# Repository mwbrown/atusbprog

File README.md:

# atusbprog

This project is intended as an exercise in learning about the following:

- Silicon Labs EFM8UB1 USB-enabled 8051 microcontroller
- Simplicity Studio for programming the EFM8UB1
- LibUSB on Linux (and possibly Windows?)
- USB in general i.e. for interacting with a microcontroller
- KiCAD design of a daughter card for the EFM8UB1 SLSTK2000A 

# Status

Currently, this project is in the very early stages where only experimentation between Linux and the SLSTK2000A have been done to toggle some LEDs, etc.

This will eventually be used as the foundation of a command/response type device that can be used to program Atmel microcontrollers. In order to accomplish this, a daughter card with one of these microcontrollers will be designed to be plugged into the side of an SLSTK2000A as an exercise in PCB design. This is not strictly required, per-se as the micros can be wired over to a breadboard, but the PCB design will prove to be a useful learning experience.

# Planned Device Support

Current plans for device support are AT89S series C51-based microcontrollers, due to their simple SPI-based programming protocol. If flash space allows, a potential addition would be supporting AVR serial programming.

A preliminary list of devices is:

* AT89S52
  - This will require some level-shifting due to the required 5V supply.
* AT89S8253
  - This can interface directly with the EFM8UB1 due to both being 3.3V chips.

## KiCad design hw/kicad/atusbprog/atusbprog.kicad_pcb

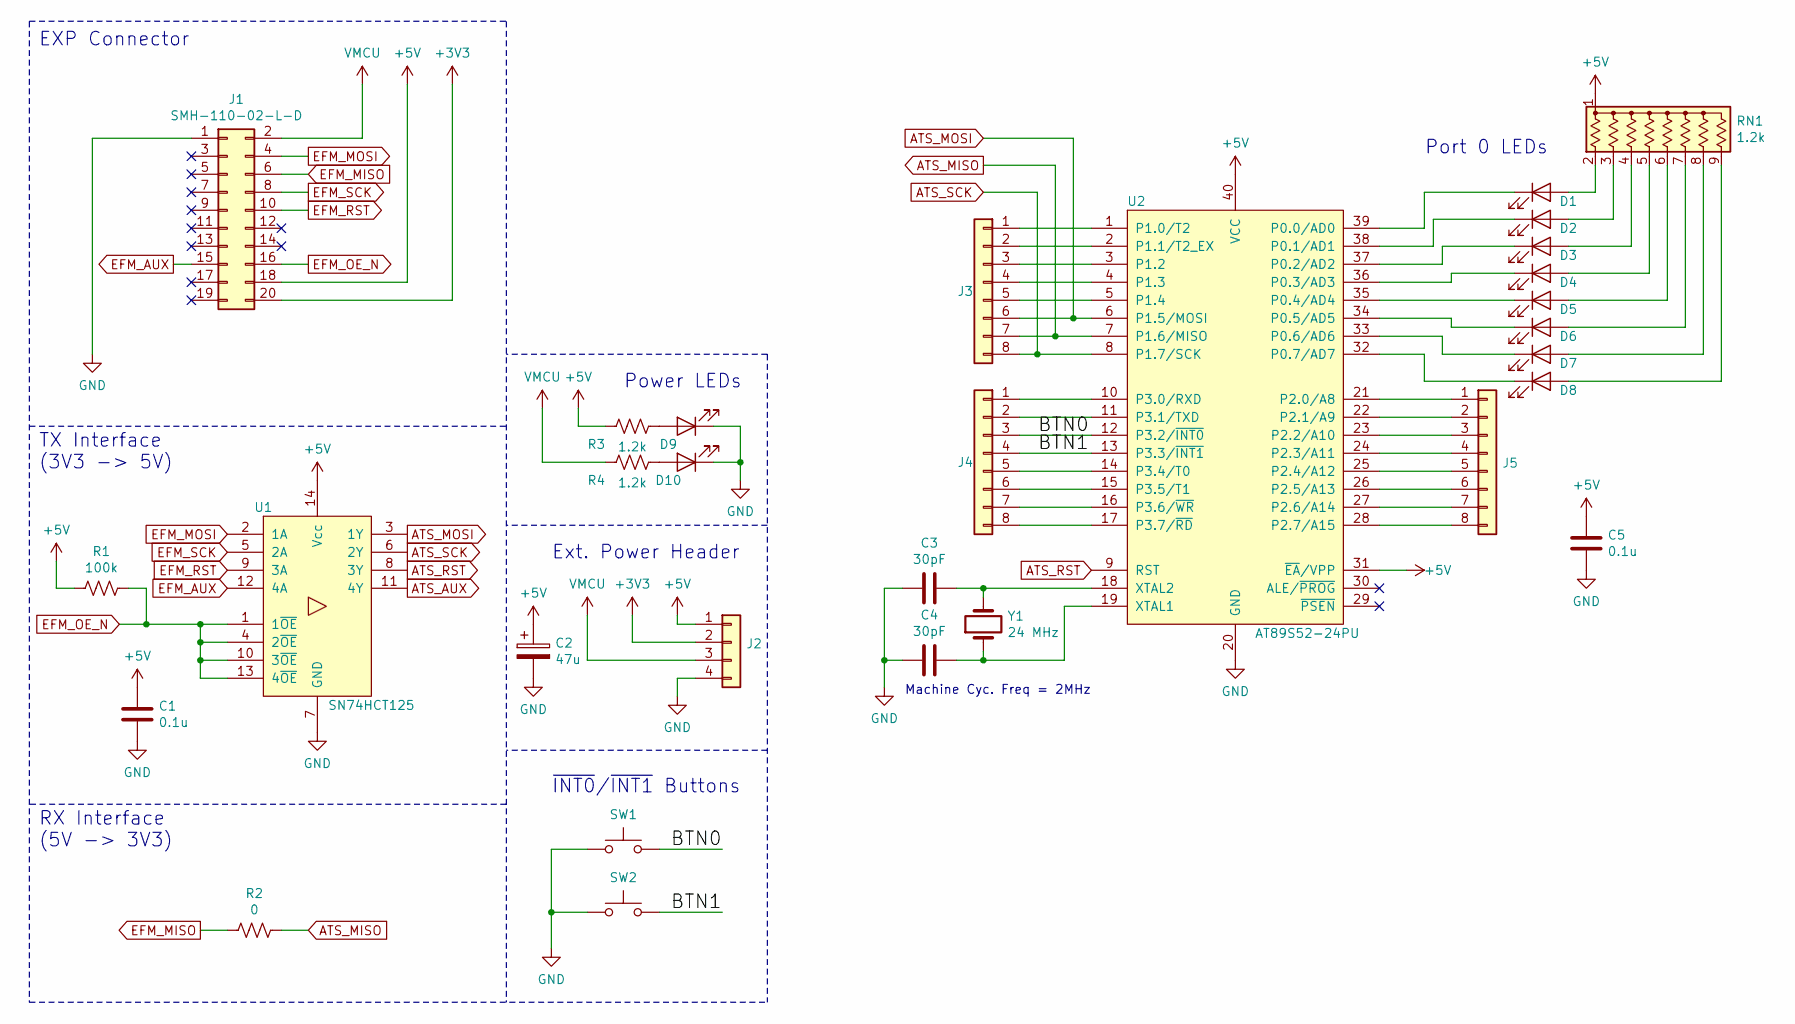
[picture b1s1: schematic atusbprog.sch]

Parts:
C1, C5: 0.1u; C_Disc_D3.8mm_W2.6mm_P2.50mm
C2: 47u; CP_Radial_D8.0mm_P3.50mm
C3, C4: 30pF; C_Disc_D3.8mm_W2.6mm_P2.50mm
D1, D2, D3, D4, D5, D6, D7, D8: LTL2R3KGD-EM; LED_D5.0mm
D9: LTL2R3KRD-EM; LED_D5.0mm
D10: LTL2R3KYD-EM; LED_D5.0mm
J1: SMH-110-02-L-D; Socket_Strip_Straight_2x10_Pitch2.54mm_SMD
J2: Conn_01x04; Pin_Header_Straight_1x04_Pitch2.54mm
J3, J4, J5: Conn_01x08; Pin_Header_Straight_1x08_Pitch2.54mm
R1: 100k; R_Axial_DIN0207_L6.3mm_D2.5mm_P7.62mm_Horizontal
R2: 0; R_Axial_DIN0207_L6.3mm_D2.5mm_P7.62mm_Horizontal
R3, R4: 1.2k; R_Axial_DIN0207_L6.3mm_D2.5mm_P7.62mm_Horizontal
RN1: 1.2k; R_Array_SIP9
SW1, SW2: SW_Push; SW_PUSH_6mm
U1: SN74HCT125; DIP-14_W7.62mm
U2: AT89S52-24PU; DIP-40_W15.24mm_LongPads
Y1: 24 MHz; Crystal_HC49-U_Vertical

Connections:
+3V3: J1.20, J2.2
+5V: C1.1, C2.1, C5.1, J1.18, J2.1, R1.2, R3.1, RN1.1 (common), U1.14 (Vcc), U2.31 (~EA~/VPP), U2.40 (VCC)
+VMCU: J1.2, J2.3, R4.1
/BTN0: J4.3, SW1.2, U2.12 (P3.2/~INT0)
/BTN1: J4.4, SW2.2, U2.13 (P3.3/~INT1)
ATS_AUX: U1.11 (4Y)
ATS_MISO: J3.7, R2.1, U2.7 (P1.6/MISO)
ATS_MOSI: J3.6, U1.3 (1Y), U2.6 (P1.5/MOSI)
ATS_RST: U1.8 (3Y), U2.9 (RST)
ATS_SCK: J3.8, U1.6 (2Y), U2.8 (P1.7/SCK)
EFM_AUX: J1.15, U1.12 (4A)
EFM_MISO: J1.6, R2.2
EFM_MOSI: J1.4, U1.2 (1A)
EFM_OE_N: J1.16, R1.1, U1.1 (1~OE), U1.4 (2~OE), U1.10 (3~OE), U1.13 (4~OE)
EFM_RST: J1.10, U1.9 (3A)
EFM_SCK: J1.8, U1.5 (2A)
GND: C1.2, C2.2, C3.2, C4.2, C5.2, D9.1 (K), D10.1 (K), J1.1, J2.4, SW1.1, SW2.1, U1.7 (GND), U2.20 (GND)
unnamed: C3.1, U2.18 (XTAL2), Y1.2
unnamed: C4.1, U2.19 (XTAL1), Y1.1
unnamed: D1.1 (K), U2.39 (P0.0/AD0)
unnamed: D1.2 (A), RN1.2 (R1)
unnamed: D2.1 (K), U2.38 (P0.1/AD1)
unnamed: D2.2 (A), RN1.3 (R2)
unnamed: D3.1 (K), U2.37 (P0.2/AD2)
unnamed: D3.2 (A), RN1.4 (R3)
unnamed: D4.1 (K), U2.36 (P0.3/AD3)
unnamed: D4.2 (A), RN1.5 (R4)
unnamed: D5.1 (K), U2.35 (P0.4/AD4)
unnamed: D5.2 (A), RN1.6 (R5)
unnamed: D6.1 (K), U2.34 (P0.5/AD5)
unnamed: D6.2 (A), RN1.7 (R6)
unnamed: D7.1 (K), U2.33 (P0.6/AD6)
unnamed: D7.2 (A), RN1.8 (R7)
unnamed: D8.1 (K), U2.32 (P0.7/AD7)
unnamed: D8.2 (A), RN1.9 (R8)
unnamed: D9.2 (A), R3.2
unnamed: D10.2 (A), R4.2
unnamed: J3.1, U2.1 (P1.0/T2)
unnamed: J3.2, U2.2 (P1.1/T2_EX)
unnamed: J3.3, U2.3 (P1.2)
unnamed: J3.4, U2.4 (P1.3)
unnamed: J3.5, U2.5 (P1.4)
unnamed: J4.1, U2.10 (P3.0/RXD)
unnamed: J4.2, U2.11 (P3.1/TXD)
unnamed: J4.5, U2.14 (P3.4/T0)
unnamed: J4.6, U2.15 (P3.5/T1)
unnamed: J4.7, U2.16 (P3.6/~WR)
unnamed: J4.8, U2.17 (P3.7/~RD)
unnamed: J5.1, U2.21 (P2.0/A8)
unnamed: J5.2, U2.22 (P2.1/A9)
unnamed: J5.3, U2.23 (P2.2/A10)
unnamed: J5.4, U2.24 (P2.3/A11)
unnamed: J5.5, U2.25 (P2.4/A12)
unnamed: J5.6, U2.26 (P2.5/A13)
unnamed: J5.7, U2.27 (P2.6/A14)
unnamed: J5.8, U2.28 (P2.7/A15)

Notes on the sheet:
EXP Connector
TX Interface (3V3 -> 5V)
Machine Cyc. Freq = 2MHz
RX Interface (5V -> 3V3)
Port 0 LEDs
~INT0~/~INT1~ Buttons
Ext. Power Header
Power LEDs

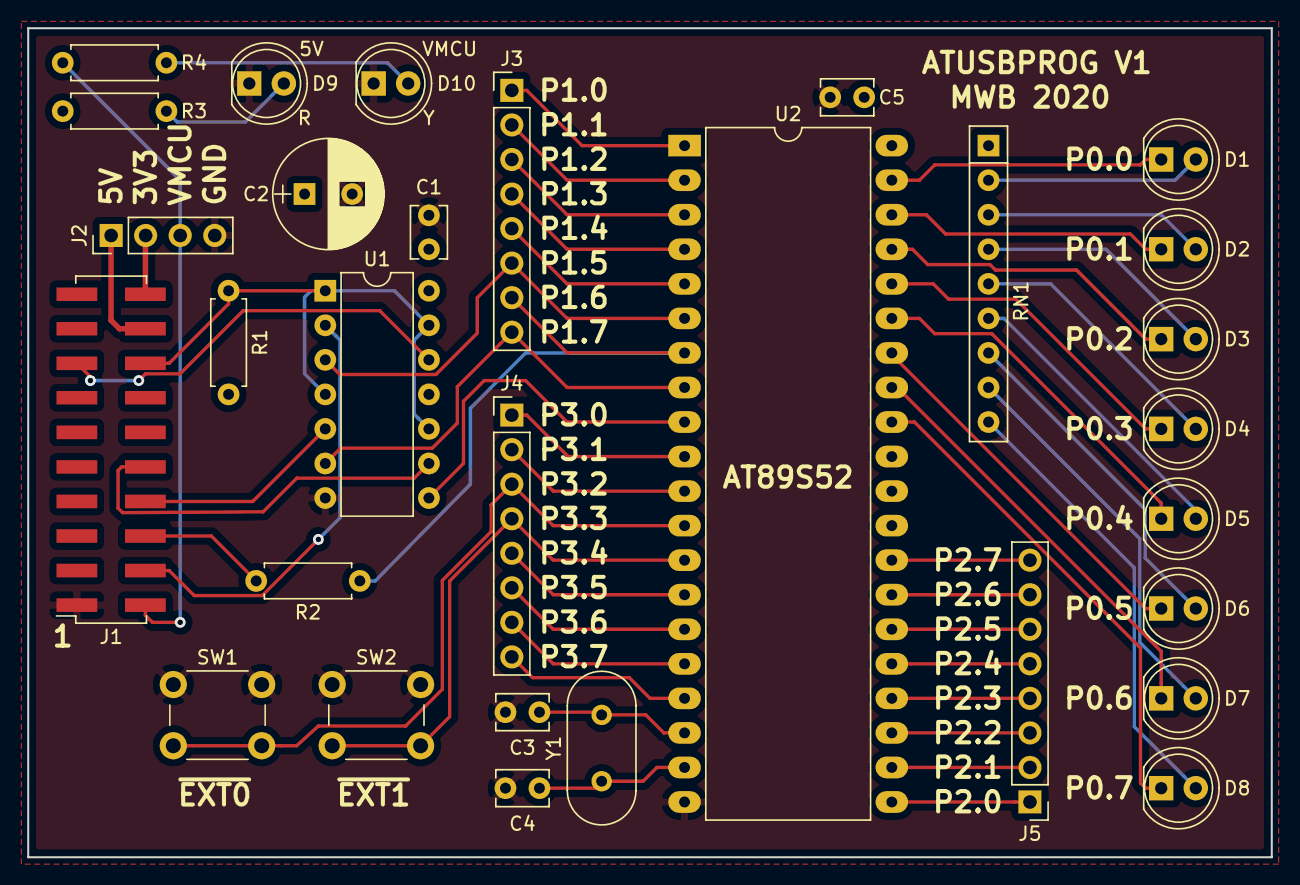
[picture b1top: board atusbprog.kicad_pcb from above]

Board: 2 copper layers, 91.4 x 61.0 mm, 30 parts (0 on the bottom side), 55 nets.

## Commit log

2020-03-26 Commit basic debug usb commands
2020-03-26 copy in linux build
2020-03-26 Ignore linux build files
2020-03-26 (wip) Change UART1->UART0, clocks, enable SPI periph xbar
2020-03-26 formatting
2020-03-26 Add inc_common directory
2020-03-26 Remove atusbprog_proto.h duplicate from linux build. Add incdir
2020-03-26 Add README
2020-03-26 Fix STK2000A -> SLSTK2000A
2020-03-26 Add blank kicad files
2020-03-30 Add Windows libusb contrib files
2020-03-30 Clarified device support plan
2020-03-30 Move host source into non-os-specific directory
2020-03-31 Add Win64 build, CMakeLists and source changes to support
2020-03-31 De-magic return code checking
2020-03-31 Update SPI clock speed.
2020-03-31 Configure P1.1 as reset out
2020-04-01 Added AT_OE_N and AT_AUX pins to FW config
2020-04-01 Added lookup table for USB command handling, cleanup.
2020-04-01 Add remaining I/Os already allocated to STK board
2020-04-01 Regenerate project from Simplicity Studio
2020-04-04 (testing) Add dummy write command
2020-04-04 Update schematic, pcb w/ unrouted rats-nest
2020-04-04 Update to KiCAD 5.1.5, add silk marks
2020-04-05 Update PCB V1
2020-04-05 Add power LEDs
2020-04-05 Move R3/R4 refdes
2020-04-05 Move power LEDs
2020-04-07 Add generated gerbers
2020-04-07 Add busy error code
2020-04-07 Update gitignore
2020-04-07 Update pcb project w/ gerber generation params
2020-04-23 First working example of programming in raw SPI mode. Add debug uart code
2020-04-23 Add system tick, shuffle around interrupts
2020-04-25 WIP Add very basic command line parser
